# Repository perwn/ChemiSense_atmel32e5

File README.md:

# ChemiSense_atmel32e5
Code for the Atmel32e5 on the circuit board.

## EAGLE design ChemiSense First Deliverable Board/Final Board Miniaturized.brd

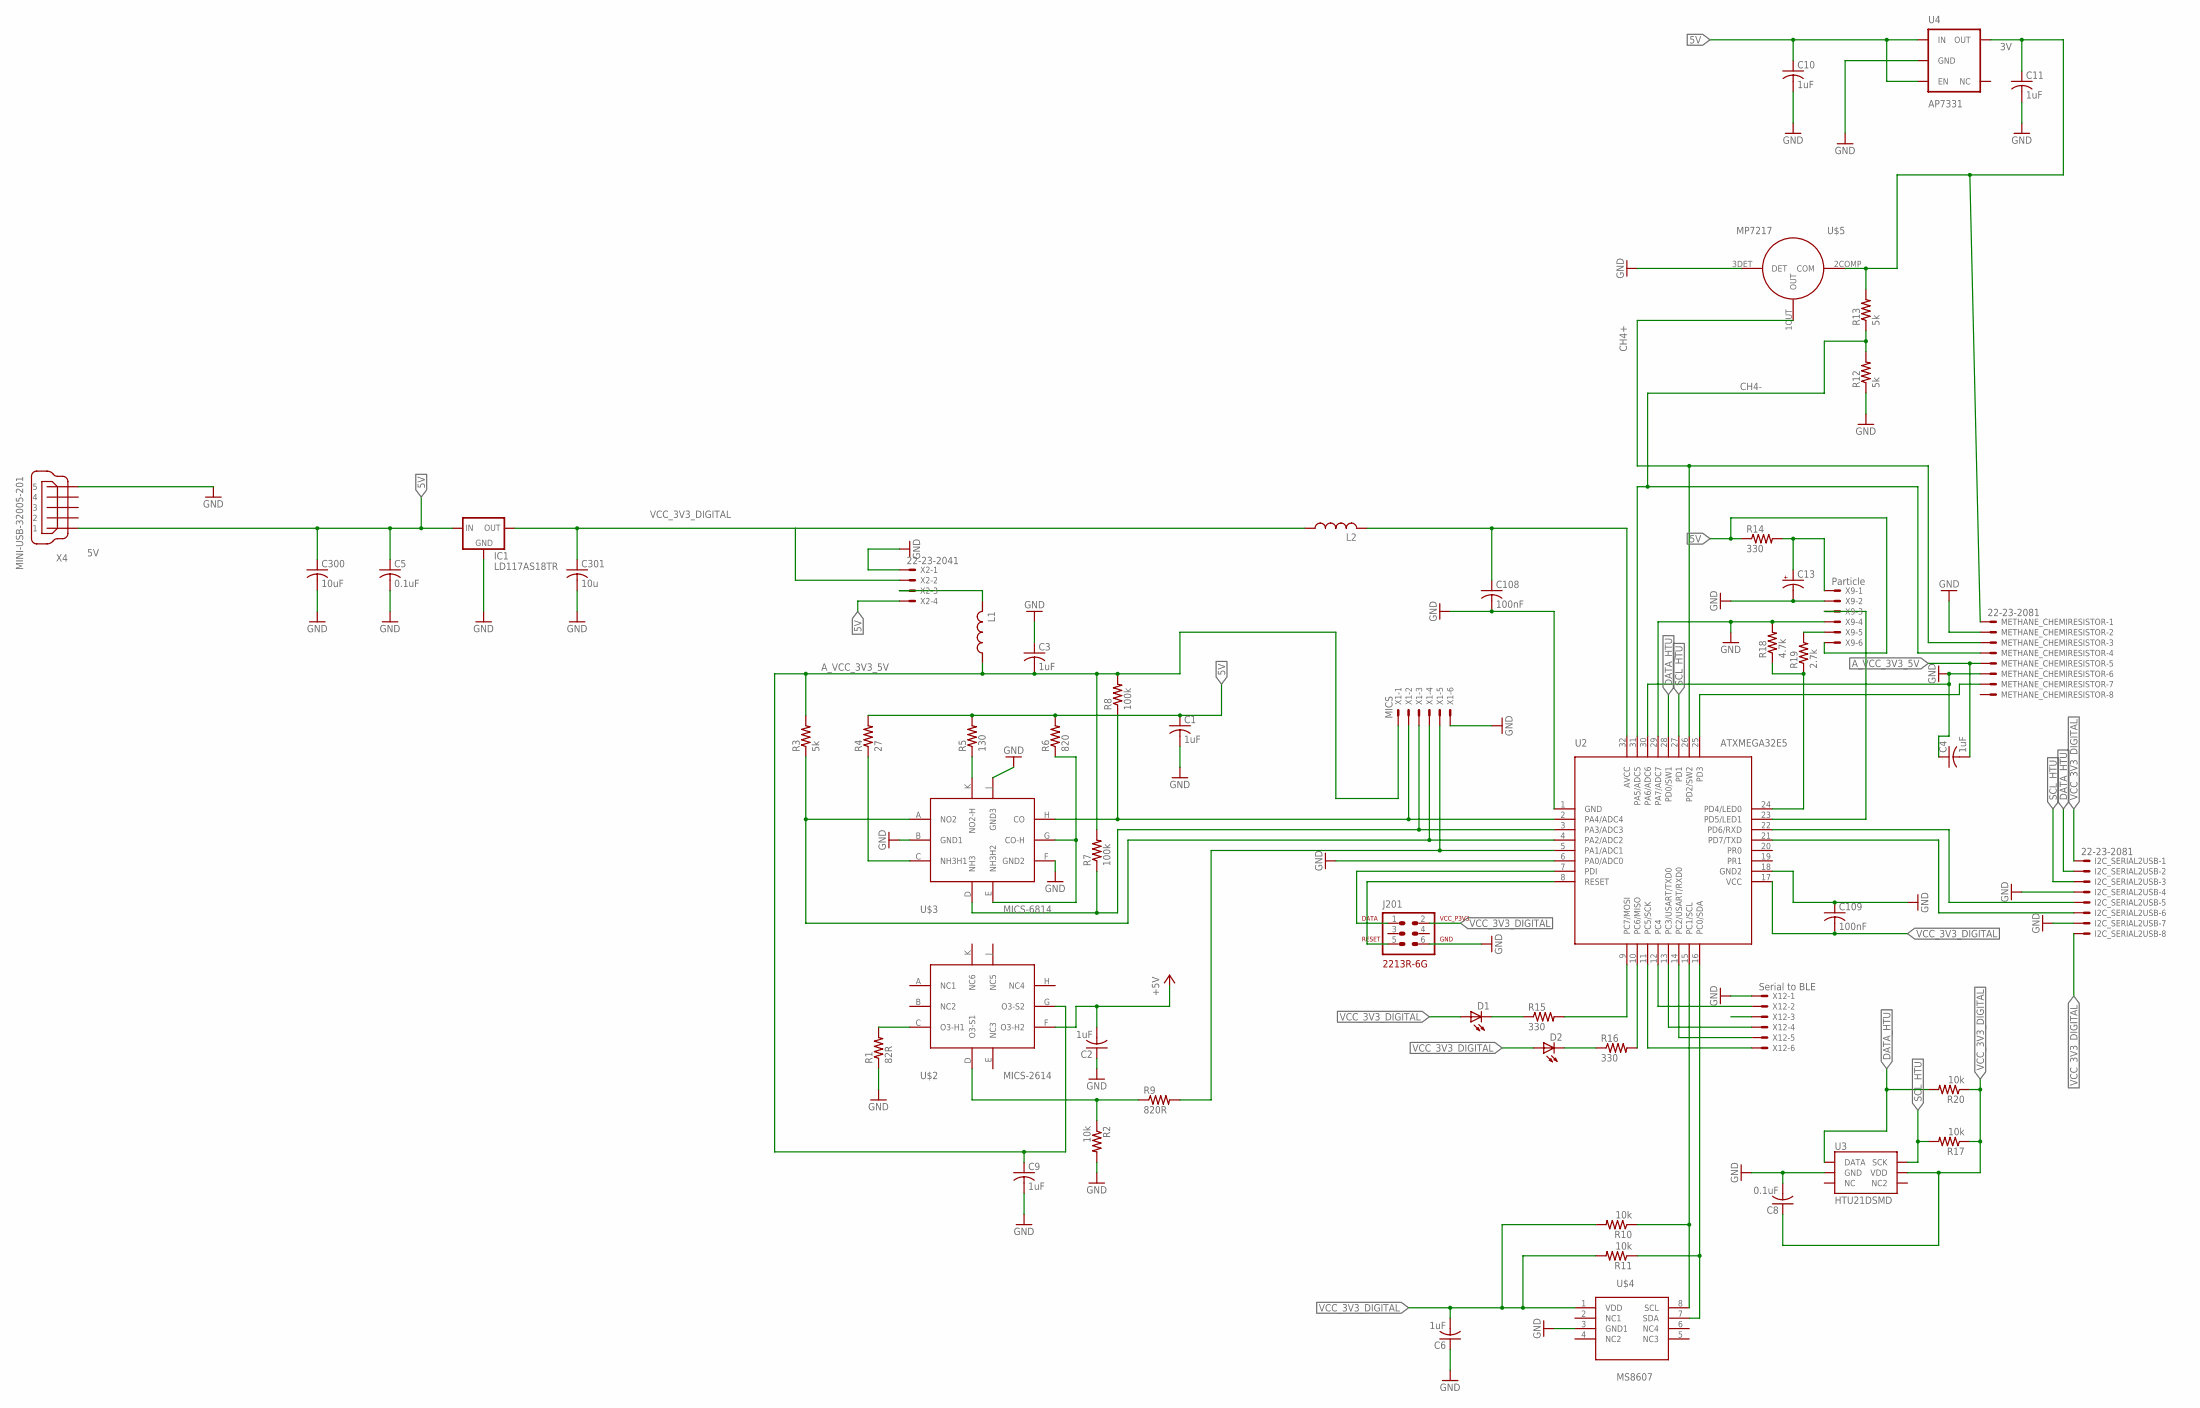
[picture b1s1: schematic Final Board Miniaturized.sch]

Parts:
C1, C2, C3, C4, C6, C9, C10, C11: 1uF; C0805
C5: 0.1uF; C0603
C8: 0.1uF; C0805
C13: CPOL-USD; PANASONIC_D
C108, C109: 100nF; C0402
C300: 10uF; C1206
C301: 10u; C1206
D1, D2: LEDSML0805; SML0805
I2C_SERIAL2USB: 22-23-2081
IC1: LD117AS18TR; SOT223
J201: PDI; AVR-ISP-6
L1, L2: 0603INDUCTOR; R0603
METHANE_CHEMIRESISTOR: 22-23-2081
R1: 82R; R0805
R2, R10, R11, R17, R20: 10k; R0805
R3, R12, R13: 5k; R0805
R4: 27; R0805
R5: 130; R0805
R6: 820; R0805
R7, R8: 100k; R0805
R9: 820R; R0805
R14, R15, R16: 330; R0402
R18: 4.7k; R0402
R19: 2.7k; R0402
U2: ATMEGA328P_TQFP; ATXMEGA32E5
U3: HTU21DSMD; HTU21D
U4: AP2202-ADJ; AP7331
U$2: MICS-2614-SMD8
U$3: MICS-6814-SMD8
U$4: PTH; PTHSENSOR
U$5: MP-7217
X1: MICS; 22-23-2061
X2: 22-23-2041
X4: MINI-USB-32005-201; 32005-201
X9: Particle; 22-23-2061
X12: Serial to BLE; 22-23-2061

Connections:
3V: C11.1, METHANE_CHEMIRESISTOR.1, R13.2, U4.5 (OUT), U$5.2COMP (COM)
5V: C1.1, C2.2, C5.1, C10.1, C300.1, IC1.3 (IN), R4.2, R5.2, R6.2, R14.1, U4.1 (IN), U4.3 (EN), U$2.F (O3-H2), X2.4, X4.1, X9.6
ADC: R9.2, U2.5 (PA1/ADC1), X1.5
AVCC_MC: C108.1, L2.2, U2.32 (AVCC)
A_VCC_3V3_5V: C3.2, C4.2, C9.1, L1.1, METHANE_CHEMIRESISTOR.5, R3.2, R7.2, R8.2, U$2.G (O3-S2), X1.1
CH4+: METHANE_CHEMIRESISTOR.3, U2.26 (PD2/SW2), U$5.1OUT (OUT)
CH4-: METHANE_CHEMIRESISTOR.4, R12.2, R13.1, U2.31 (PA5/ADC5)
DATA_HTU: I2C_SERIAL2USB.2, R20.2, U2.28 (PD0/SW1), U3.DATA
GND: C1.2, C2.1, C3.1, C4.1, C5.2, C6.1, C8.2, C9.2, C10.2, C11.2, C13.-, C108.2, C109.1, C300.2, C301.2, I2C_SERIAL2USB.4, I2C_SERIAL2USB.7, IC1.1 (GND), J201.6 (GND), METHANE_CHEMIRESISTOR.2, METHANE_CHEMIRESISTOR.6, R1.1, R2.2, R12.1, R18.2, U2.1 (GND), U2.6 (PA0/ADC0), U2.18 (GND2), U2.29 (PA7/ADC7), U2.30 (PA6/ADC6), U3.GND, U4.2 (GND), U$3.B (GND1), U$3.F (GND2), U$3.J (GND3), U$4.3 (GND1), U$5.3DET (DET), X1.6, X2.1, X4.5, X9.2, X9.4, X12.1
IC1: R3.1, U2.4 (PA2/ADC2), U$3.A (NO2), X1.4
unnamed: R1.2, U$2.C (O3-H1)
unnamed: J201.1 (DATA), U2.7 (PDI)
unnamed: J201.5 (RESET), U2.8 (RESET)
unnamed: R16.2, U2.10 (PC6/MISO)
unnamed: METHANE_CHEMIRESISTOR.7, U2.25 (PD3)
unnamed: I2C_SERIAL2USB.5, U2.22 (PD6/RXD)
unnamed: R7.1, U2.3 (PA3/ADC3), U$3.D (NH3), X1.3
unnamed: R6.1, U$3.E (NH3H2), U$3.G (CO-H)
unnamed: R5.1, U$3.K (NO2-H)
unnamed: R4.1, U$3.C (NH3H1)
unnamed: R8.1, U2.2 (PA4/ADC4), U$3.H (CO), X1.2
unnamed: R10.1, U2.15 (PC1/SCL), U$4.8 (SCL)
unnamed: R18.1, R19.1, U2.24 (PD4/LED0)
unnamed: U2.23 (PD5/LED1), X9.3
unnamed: R11.1, U2.16 (PC0/SDA), U$4.7 (SDA)
unnamed: R19.2, X9.5
unnamed: U2.13 (PC3/USART/TXD0), X12.4
unnamed: U2.14 (PC2/USART/RXD0), X12.5
unnamed: R2.1, R9.1, U$2.D (O3-S1)
unnamed: C13.+, R14.2, X9.1
unnamed: L1.2, X2.3
unnamed: I2C_SERIAL2USB.6, U2.21 (PD7/TXD)
unnamed: D1.C, R15.1
unnamed: U2.12 (PC4), X12.2
unnamed: D2.C, R16.1
unnamed: R15.2, U2.9 (PC7/MOSI)
unnamed: U2.11 (PC5/SCK), X12.6
NC: U3.NC@1 (NC)
SCL_HTU: I2C_SERIAL2USB.3, R17.2, U2.27 (PD1), U3.SCK
VCC_3V3_DIGITAL: C6.2, C8.1, C109.2, C301.1, D1.A, D2.A, I2C_SERIAL2USB.1, I2C_SERIAL2USB.8, IC1.2 (OUT), J201.2 (VCC_P3V3), L2.1, R10.2, R11.2, R17.1, R20.1, U2.17 (VCC), U3.VDD, U$4.1 (VDD), X2.2

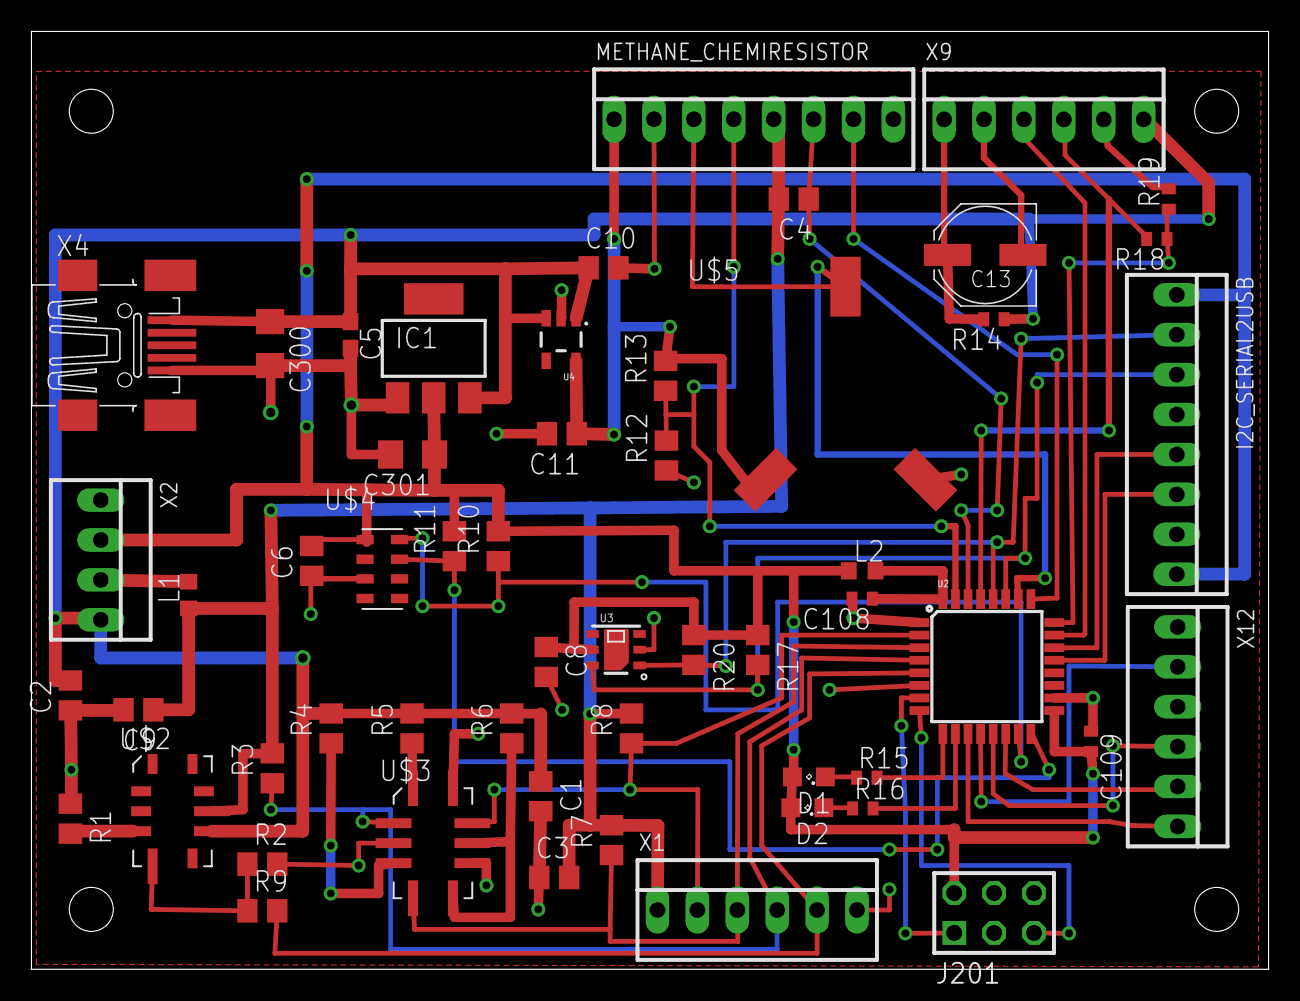
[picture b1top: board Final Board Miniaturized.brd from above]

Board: 2 copper layers, 78.7 x 59.7 mm, 55 parts (0 on the bottom side), 39 nets.

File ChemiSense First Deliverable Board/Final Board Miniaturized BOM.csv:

"Part";"Value";"Device";"Package";"Description";"MF";"MPN";"OC_FARNELL";"OC_NEWARK";"PROD_ID";"VALUE";
"C1";"1uF";"C-USC0805";"C0805";"CAPACITOR, American symbol";"";"";"";"";"";"";
"C2";"1uF";"C-USC0805";"C0805";"CAPACITOR, American symbol";"";"";"";"";"";"";
"C3";"1uF";"C-USC0805";"C0805";"CAPACITOR, American symbol";"";"";"";"";"";"";
"C4";"1uF";"C-USC0805";"C0805";"CAPACITOR, American symbol";"";"";"";"";"";"";
"C5";"0.1uF";"C-USC0603";"C0603";"CAPACITOR, American symbol";"";"";"";"";"";"";
"C6";"1uF";"C-USC0805";"C0805";"CAPACITOR, American symbol";"";"";"";"";"";"";
"C8";"0.1uF";"C-USC0805";"C0805";"CAPACITOR, American symbol";"";"";"";"";"";"";
"C9";"1uF";"C-USC0805";"C0805";"CAPACITOR, American symbol";"";"";"";"";"";"";
"C10";"1uF";"C-USC0805";"C0805";"CAPACITOR, American symbol";"";"";"";"";"";"";
"C11";"1uF";"C-USC0805";"C0805";"CAPACITOR, American symbol";"";"";"";"";"";"";
"C13";"";"CPOL-USD";"PANASONIC_D";"POLARIZED CAPACITOR, American symbol";"";"";"";"";"";"";
"C108";"100nF";"C-USC0402";"C0402";"CAPACITOR, American symbol";"";"";"";"";"";"";
"C109";"100nF";"C-USC0402";"C0402";"CAPACITOR, American symbol";"";"";"";"";"";"";
"C300";"10uF";"C-USC1206";"C1206";"CAPACITOR, American symbol";"";"";"";"";"";"";
"C301";"10u";"C-USC1206";"C1206";"CAPACITOR, American symbol";"";"";"";"";"";"";
"D1";"";"LEDSML0805";"SML0805";"LED";"";"";"";"";"";"";
"D2";"";"LEDSML0805";"SML0805";"LED";"";"";"";"";"";"";
"I2C_SERIAL2USB";"22-23-2081";"22-23-2081";"22-23-2081";".100" (2.54mm) Center Header - 8 Pin";"MOLEX";"22-23-2081";"1756826";"01C7592";"";"";
"IC1";"LD117AS18TR";"LD117AS18TR";"SOT223";"Low drop fixed and adjustable positive voltage regulators 1 A";"";"";"";"";"";"";
"J201";"PDI";"AVR-ISP-6";"AVR-ISP-6";"PDI Interface for XMEGA";"";"";"";"";"";"";
"L1";"";"0603INDUCTOR";"R0603";"INDUCTOR, American symbol";"";"";"";"";"";"";
"L2";"";"0603INDUCTOR";"R0603";"INDUCTOR, American symbol";"";"";"";"";"";"";
"METHANE_CHEMIRESISTOR";"22-23-2081";"22-23-2081";"22-23-2081";".100" (2.54mm) Center Header - 8 Pin";"MOLEX";"22-23-2081";"1756826";"01C7592";"";"";
"R1";"82R";"R-US_R0805";"R0805";"RESISTOR, American symbol";"";"";"";"";"";"";
"R2";"10k";"R-US_R0805";"R0805";"RESISTOR, American symbol";"";"";"";"";"";"";
"R3";"5k";"R-US_R0805";"R0805";"RESISTOR, American symbol";"";"";"";"";"";"";
"R4";"27";"R-US_R0805";"R0805";"RESISTOR, American symbol";"";"";"";"";"";"";
"R5";"130";"R-US_R0805";"R0805";"RESISTOR, American symbol";"";"";"";"";"";"";
"R6";"820";"R-US_R0805";"R0805";"RESISTOR, American symbol";"";"";"";"";"";"";
"R7";"100k";"R-US_R0805";"R0805";"RESISTOR, American symbol";"";"";"";"";"";"";
"R8";"100k";"R-US_R0805";"R0805";"RESISTOR, American symbol";"";"";"";"";"";"";
"R9";"820R";"R-US_R0805";"R0805";"RESISTOR, American symbol";"";"";"";"";"";"";
"R10";"10k";"R-US_R0805";"R0805";"RESISTOR, American symbol";"";"";"";"";"";"";
"R11";"10k";"R-US_R0805";"R0805";"RESISTOR, American symbol";"";"";"";"";"";"";
"R12";"5k";"R-US_R0805";"R0805";"RESISTOR, American symbol";"";"";"";"";"";"";
"R13";"5k";"R-US_R0805";"R0805";"RESISTOR, American symbol";"";"";"";"";"";"";
"R14";"330";"R-US_R0402";"R0402";"RESISTOR, American symbol";"";"";"";"";"";"";
"R15";"330";"R-US_R0402";"R0402";"RESISTOR, American symbol";"";"";"";"";"";"";
"R16";"330";"R-US_R0402";"R0402";"RESISTOR, American symbol";"";"";"";"";"";"";
"R17";"10k";"R-US_R0805";"R0805";"RESISTOR, American symbol";"";"";"";"";"";"";
"R18";"4.7k";"R-US_R0402";"R0402";"RESISTOR, American symbol";"";"";"";"";"";"";
"R19";"2.7k";"R-US_R0402";"R0402";"RESISTOR, American symbol";"";"";"";"";"";"";
"R20";"10k";"R-US_R0805";"R0805";"RESISTOR, American symbol";"";"";"";"";"";"";
"U$2";"MICS-2614-SMD8";"MICS-2614-SMD8";"MICS-2614-SMD8";"MICS-6814, NO2, NH3, CO";"";"";"";"";"";"";
"U$3";"MICS-6814-SMD8";"MICS-6814-SMD8";"MICS-6814-SMD8";"MICS-6814, NO2, NH3, CO";"";"";"";"";"";"";
"U$4";"PTH";"PTH";"PTHSENSOR";"PTH Sensor from Measurement Specialties";"";"";"";"";"";"";
"U$5";"MP-7217";"MP-7217";"MP-7217";"Methane Sensor (Pellistor)";"";"";"";"";"";"";
"U2";"ATMEGA328P_TQFP";"ATXMEGA32E5";"ATXMEGA32E5";"Microcontroller by Atmel";"";"";"";"";"IC-09069";"ATMEGA328P_TQFP";
"U3";"HTU21DSMD";"HTU21DSMD";"HTU21D";"";"";"";"";"";"IC-11793";"";
"U4";"AP2202-ADJ";"AP7331";"AP7331";"3V Voltage Regulator from Diodes, Inc.";"";"";"";"";"VREG-12189";"AP2202-ADJ";
"X1";"MICS";"22-23-2061";"22-23-2061";".100" (2.54mm) Center Header - 6 Pin";"MOLEX";"22-23-2061";"1462922";"27C1933";"";"";
"X2";"22-23-2041";"22-23-2041";"22-23-2041";".100" (2.54mm) Center Header - 4 Pin";"MOLEX";"22-23-2041";"1462920";"38C0355";"";"";
"X4";"MINI-USB-32005-201";"MINI-USB-32005-201";"32005-201";"MINI USB-B Conector";"";"";"unknown";"unknown";"";"";
"X9";"Particle";"22-23-2061";"22-23-2061";".100" (2.54mm) Center Header - 6 Pin";"MOLEX";"22-23-2061";"1462922";"27C1933";"";"";
"X12";"Serial to BLE";"22-23-2061";"22-23-2061";".100" (2.54mm) Center Header - 6 Pin";"MOLEX";"22-23-2061";"1462922";"27C1933";"";"";

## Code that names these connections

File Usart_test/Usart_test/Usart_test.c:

/*
 * Usart_test.c
 *
 * Created: 6/18/2015 1:07:29 PM
 *  Author: ChemiSenseUser
 */ 
#define F_CPU 32000000UL
//#define BAUD 9600

#include <avr/io.h>
#include <avr/interrupt.h>
#include <util/delay.h>
//#include <avr/instdio.h>
//#include <util/setbaud.h>


static void usart_write(uint8_t data)
{
	USARTD0.DATA = data;
	if(!(USARTD0.STATUS & USART_DREIF_bm)) {
		while(!(USARTD0.STATUS & USART_TXCIF_bm)); // wait for TX complete
	}
	USARTD0.STATUS |= USART_TXCIF_bm;  // clear TX interrupt flag
}

static void usart_write_string(char *text){
	
	PORTA.OUTSET = PIN0_bm;
	while(*text)
	{
		usart_write(*text++);
	}
	PORTA.OUTCLR = PIN0_bm;
}
static inline void init_oscillator() {
	// enable 32Mhz internal oscillator
	OSC.CTRL |= OSC_RC32MEN_bm;
	// wait for it to be stable
	while (!(OSC.STATUS & OSC_RC32MRDY_bm));
	// tell the processor we want to change a protected register
	CCP=CCP_IOREG_gc;
	// and start using the 32Mhz oscillator
	CLK.CTRL=CLK_SCLKSEL_RC32M_gc;
	// disable the default 2Mhz oscillator
	OSC.CTRL&=(~OSC_RC2MEN_bm);
	// enable 32kHz calibrated internal oscillator
	OSC.CTRL|= OSC_RC32KEN_bm;
	while (!(OSC.STATUS & OSC_RC32KRDY_bm));
	// set bit to 0 to indicate we use the internal 32kHz
	// callibrated oscillator as auto-calibration source
	// for our 32Mhz oscillator
	OSC.DFLLCTRL = OSC_RC32MCREF_RC32K_gc;
	// enable auto-calibration for the 32Mhz oscillator
	DFLLRC32M.CTRL |= DFLL_ENABLE_bm;
}

static inline void init_usart() {
	// enable clock out on port PC7
	PORTCFG.CLKOUT = (PORTCFG.CLKOUT & ~PORTCFG_CLKOUTSEL_gm) | PORTCFG_CLKOUT_PC7_gc;
	// set PC7 as output
	PORTC.DIRSET = PIN7_bm;

	// set PD7 as output for TX0
	PORTD.DIRSET = PIN7_bm;
	PORTD.OUTSET = PIN7_bm;
	// remap USARTD0 to PD[7-4]
	PORTD.REMAP |= PORT_USART0_bm;
	// set baud rate 9600: BSEL=12, BSCALE=4
	// as found in table in
	// Atmel-42005-8-and-16-bit-AVR-Microcontrollers-XMEGA-E_Manual.pdf
	USARTD0.BAUDCTRLA = 12; // BSEL
	USARTD0.BAUDCTRLB = 4 << USART_BSCALE_gp; // BSCALE
	// disable 2X
	USARTD0.CTRLB = USARTD0.CTRLB & ~USART_CLK2X_bm;
	// enable RX and TX
	USARTD0.CTRLB = USARTD0.CTRLB | USART_RXEN_bm | USART_TXEN_bm;
	// enable async UART 8N1
	USARTD0.CTRLC = USART_CMODE_ASYNCHRONOUS_gc | USART_PMODE_DISABLED_gc | USART_CHSIZE_8BIT_gc;
	USARTD0.CTRLC &= ~USART_SBMODE_bm;
	USARTD0.CTRLD = 0; // No LUT

	// set interrupt level for RX
	USARTD0.CTRLA = (USARTD0.CTRLA & ~USART_RXCINTLVL_gm) | USART_RXCINTLVL_LO_gc;
}

static inline void init_interrupts() {
	// Enable PMIC interrupt level low
	PMIC.CTRL |= PMIC_LOLVLEX_bm;
	// enable interrupts
	sei();
}



static volatile uint8_t echo_char = 42;

int main( void )
{
	init_oscillator();

	// enable clock out on port PC7
	PORTCFG.CLKOUT = (PORTCFG.CLKOUT & ~PORTCFG_CLKOUTSEL_gm) | PORTCFG_CLKOUT_PC7_gc;
	// set PC7 as output
	PORTC.DIRSET = PIN7_bm;

	init_usart();

	init_interrupts();

	// set PA0 as output
	PORTA.DIRSET = PIN0_bm;
	// blink LED on PA0 with 1 second on, 1 second off
	// write echo_char on USART on D7; defaults to 42(*)
	while (1) {
		usart_write_string("abc\n");
		_delay_ms(500);
	}
}

// USART RX receive interrupt handler
ISR(USARTD0_RXC_vect) {
	echo_char = USARTD0.DATA;
}









/*

static int uart_putchar(char c, FILE *stream);

// extern "C"{ FILE * uart_str; }


void setUp32MhzInternalOsc()
{
	OSC_CTRL |= OSC_RC32MEN_bm; //Setup 32Mhz crystal
	
	while(!(OSC_STATUS & OSC_RC32MRDY_bm));
	
	CCP = CCP_IOREG_gc; //Trigger protection mechanism
	CLK_CTRL = CLK_SCLKSEL_RC32M_gc; //Enable internal  32Mhz crystal
	
	
}

void setUpSerial()
{
	//For the sake of example, I'll just REMAP the USART pins from PC3 and PC2 to PC7 and PC6
	PORTC_REMAP |= 0x16; //See page 152 in datasheet, remaps the USART0
		
	PORTC_OUTSET = PIN7_bm; //Let's make PC7 as TX
	PORTC_DIRSET = PIN7_bm; //TX pin as output
		
	PORTC_OUTCLR = PIN6_bm;
	PORTC_DIRCLR = PIN6_bm; //PC6 as RX
	
	// Baud rate selection
	// BSEL = (32000000 / (2^0 * 16*9600) -1 = 207.333 -> BSCALE = 0
	// FBAUD = ( (32000000)/(2^0*16(207+1)) = 9615.384 -> it's alright
	
	USARTC0_BAUDCTRLB = 0; //Just to be sure that BSCALE is 0
	USARTC0_BAUDCTRLA = 0xCF; // 207
	
	
	//Disable interrupts, just for safety
	USARTC0_CTRLA = 0;
	//8 data bits, no parity and 1 stop bit
	USARTC0_CTRLC = USART_CHSIZE_8BIT_gc;
	
	//Enable receive and transmit
	USARTC0_CTRLB = USART_TXEN_bm | USART_RXEN_bm; // And enable high speed mode
}

void sendChar(char c)
{
	
	while( !(USARTC0_STATUS & USART_DREIF_bm) ); //Wait until DATA buffer is empty
	
	USARTC0_DATA = c;
	
}

void sendString(char *text)
{
	while(*text)
	{
		sendChar(*text++);
	}
}
 
 static int uart_putchar (char c, FILE *stream)
 {
	 if (c == '\n')
	 uart_putchar('\r', stream);
	 
	 // Wait for the transmit buffer to be empty
	 while (  !(USARTC0_STATUS & USART_DREIF_bm) );
	 
	 // Put our character into the transmit buffer
	 USARTC0_DATA = c;
	 
	 return 0;
 }

char usart_receiveByte()
{
	while( !(USARTC0_STATUS & USART_RXCIF_bm) ); //Interesting DRIF didn't work.
	return USARTC0_DATA;
}

int uart_getchar(FILE *stream)
{
	while( !(USARTC0_STATUS & USART_RXCIF_bm) ); //Interesting DRIF didn't work.
	char data = USARTC0_DATA;
	if(data == '\r'){
		data = '\n';		
	}
	uart_putchar(data, stream);
	return data;
}

FILE usart_str = FDEV_SETUP_STREAM(uart_putchar, uart_getchar, _FDEV_SETUP_RW);

int main()
{
	setUp32MhzInternalOsc();
	setUpSerial();
	
//	File uart_str = fdevopen(uart_putchar, uart_getchar);
	stdout = stdin = &usart_str;
	
	printf("Ready!\n");
    printf("Ready!\n");
    while(1)
    {
	 printf ("A");
	 _delay_ms(500);
	  //  char str [80];
	  //  int i;
	  //  printf ("Enter your family name: ");
	  //  scanf ("%79s",str);
	  //  printf ("Enter your age: ");
	  //  scanf ("%d",&i);
	  //  printf ("Mr. %s , %d years old.\n",str,i);
	}
}
*/

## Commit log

2015-06-19 old files
2015-06-25 backup
2015-06-26 Eagle files + datasheets

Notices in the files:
parts and their libraries:
SparkFun-Sensors: Licensing: Creative Commons ShareAlike 4.0 International - https://creativecommons.org/licenses/by-sa/4.0
